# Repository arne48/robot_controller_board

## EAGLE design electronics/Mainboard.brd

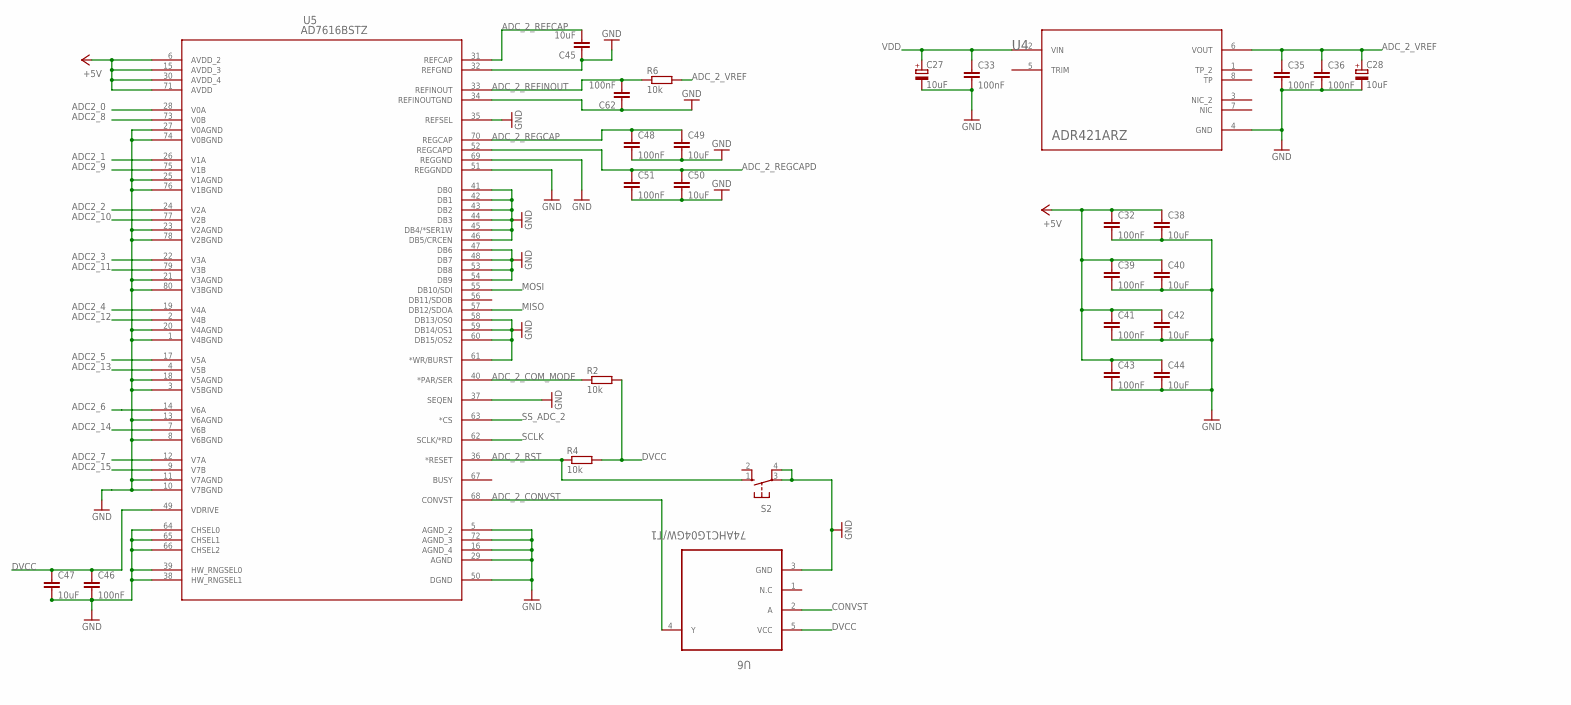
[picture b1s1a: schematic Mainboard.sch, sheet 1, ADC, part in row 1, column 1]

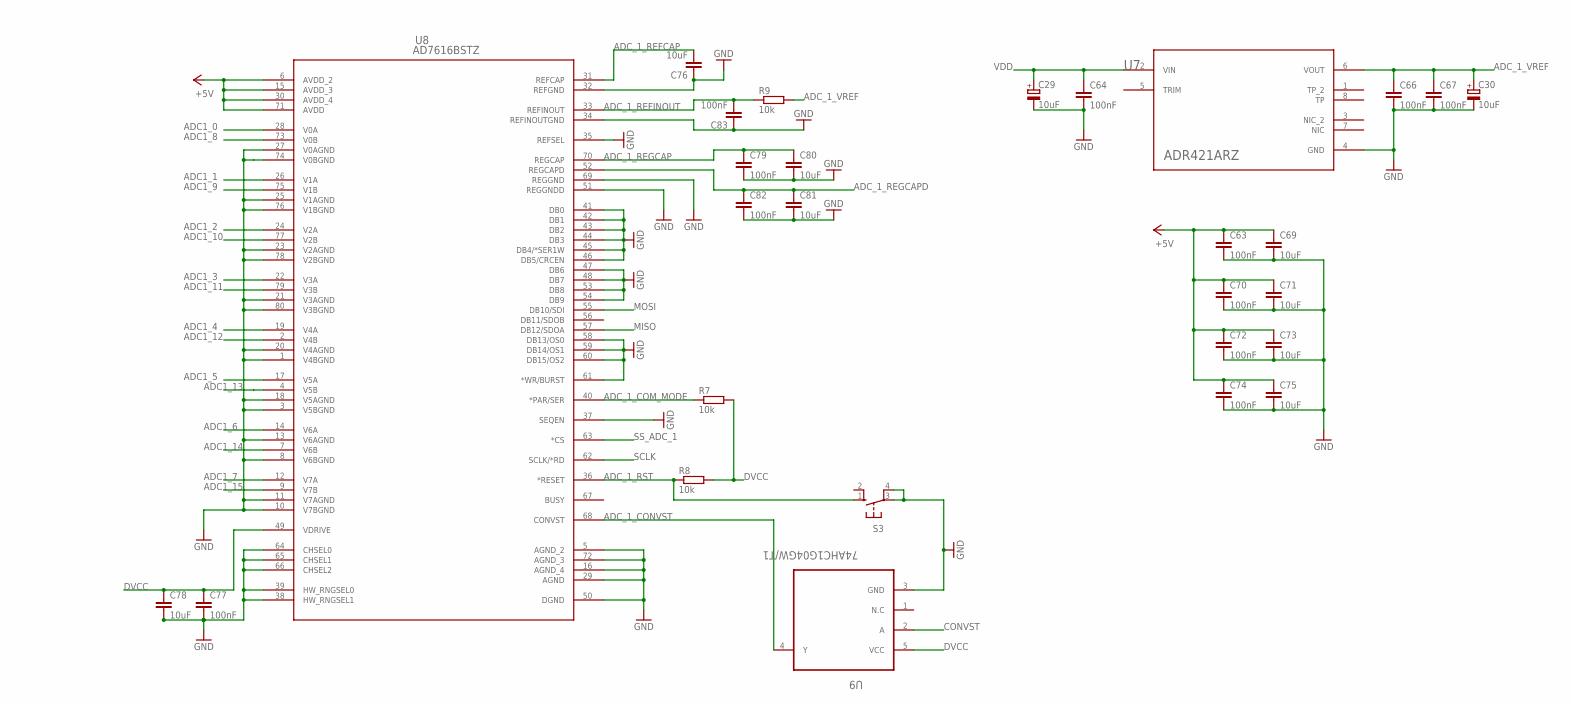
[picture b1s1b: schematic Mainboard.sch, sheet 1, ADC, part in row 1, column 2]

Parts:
C27, C28, C29, C30: 10uF; SMC_A
C32, C33, C35, C36, C39, C41, C43, C46, C48, C51, C62, C63, C64, C66, C67, C70, C72, C74, C77, C79, C82, C83: 100nF; C0603
C38, C40, C42, C44, C45, C47, C49, C50, C69, C71, C73, C75, C76, C78, C80, C81: 10uF; C0603
R2, R4, R6, R7, R8, R9: 10k; R0603
S2, S3: 10-XX; B3F-10XX
U4, U7: ADR421ARZ; R_8
U5, U8: AD7616BSTZ; ST_80_2
U6, U9: 74AHC1G04GW/T1; SOT65P210X110-5N

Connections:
+5V: C32.1, C38.1, C39.1, C40.1, C41.1, C42.1, C43.1, C44.1, C63.1, C69.1, C70.1, C71.1, C72.1, C73.1, C74.1, C75.1, U5.6 (AVDD_2), U5.15 (AVDD_3), U5.30 (AVDD_4), U5.71 (AVDD), U8.6 (AVDD_2), U8.15 (AVDD_3), U8.30 (AVDD_4), U8.71 (AVDD); also elsewhere on the board
ADC1_0: U8.28 (V0A); also elsewhere on the board
ADC1_1: U8.26 (V1A); also elsewhere on the board
ADC1_2: U8.24 (V2A); also elsewhere on the board
ADC1_3: U8.22 (V3A); also elsewhere on the board
ADC1_4: U8.19 (V4A); also elsewhere on the board
ADC1_5: U8.17 (V5A); also elsewhere on the board
ADC1_6: U8.14 (V6A); also elsewhere on the board
ADC1_7: U8.12 (V7A); also elsewhere on the board
ADC1_8: U8.73 (V0B); also elsewhere on the board
ADC1_9: U8.75 (V1B); also elsewhere on the board
ADC1_10: U8.77 (V2B); also elsewhere on the board
ADC1_11: U8.79 (V3B); also elsewhere on the board
ADC1_12: U8.2 (V4B); also elsewhere on the board
ADC1_13: U8.4 (V5B); also elsewhere on the board
ADC1_14: U8.7 (V6B); also elsewhere on the board
ADC1_15: U8.9 (V7B); also elsewhere on the board
ADC2_0: U5.28 (V0A); also elsewhere on the board
ADC2_1: U5.26 (V1A); also elsewhere on the board
ADC2_2: U5.24 (V2A); also elsewhere on the board
ADC2_3: U5.22 (V3A); also elsewhere on the board
ADC2_4: U5.19 (V4A); also elsewhere on the board
ADC2_5: U5.17 (V5A); also elsewhere on the board
ADC2_6: U5.14 (V6A); also elsewhere on the board
ADC2_7: U5.12 (V7A); also elsewhere on the board
ADC2_8: U5.73 (V0B); also elsewhere on the board
ADC2_9: U5.75 (V1B); also elsewhere on the board
ADC2_10: U5.77 (V2B); also elsewhere on the board
ADC2_11: U5.79 (V3B); also elsewhere on the board
ADC2_12: U5.2 (V4B); also elsewhere on the board
ADC2_13: U5.4 (V5B); also elsewhere on the board
ADC2_14: U5.7 (V6B); also elsewhere on the board
ADC2_15: U5.9 (V7B); also elsewhere on the board
ADC_1_COM_MODE: R7.1, U8.40 (*PAR/SER)
ADC_1_CONVST: U8.68 (CONVST), U9.4 (Y)
ADC_1_REFCAP: C76.2, U8.31 (REFCAP)
ADC_1_REFINOUT: C83.2, R9.1, U8.33 (REFINOUT)
ADC_1_REGCAP: C79.1, C80.1, U8.70 (REGCAP)
ADC_1_REGCAPD: C81.1, C82.1, U8.52 (REGCAPD)
ADC_1_RST: R8.1, S3.1 (S), U8.36 (*RESET)
ADC_1_VREF: C30.+, C66.1, C67.1, R9.2, U7.6 (VOUT)
ADC_2_COM_MODE: R2.1, U5.40 (*PAR/SER)
ADC_2_CONVST: U5.68 (CONVST), U6.4 (Y)
ADC_2_REFCAP: C45.2, U5.31 (REFCAP)
ADC_2_REFINOUT: C62.2, R6.1, U5.33 (REFINOUT)
ADC_2_REGCAP: C48.1, C49.1, U5.70 (REGCAP)
ADC_2_REGCAPD: C50.1, C51.1, U5.52 (REGCAPD)
ADC_2_RST: R4.1, S2.1 (S), U5.36 (*RESET)
ADC_2_VREF: C28.+, C35.1, C36.1, R6.2, U4.6 (VOUT)
CONVST: U6.2 (A), U9.2 (A); also elsewhere on the board
DVCC: C46.1, C47.1, C77.1, C78.1, R2.2, R4.2, R7.2, R8.2, U5.49 (VDRIVE), U6.5 (VCC), U8.49 (VDRIVE), U9.5 (VCC); also elsewhere on the board
GND: C27.-, C28.-, C29.-, C30.-, C32.2, C33.2, C35.2, C36.2, C38.2, C39.2, C40.2, C41.2, C42.2, C43.2, C44.2, C45.1, C46.2, C47.2, C48.2, C49.2, C50.2, C51.2, C62.1, C63.2, C64.2, C66.2, C67.2, C69.2, C70.2, C71.2, C72.2, C73.2, C74.2, C75.2, C76.1, C77.2, C78.2, C79.2, C80.2, C81.2, C82.2, C83.1, S2.3, S2.4 (P1), S3.3, S3.4 (P1), U4.4 (GND), U5.1 (V4BGND), U5.3 (V5BGND), U5.5 (AGND_2), U5.8 (V6BGND), U5.10 (V7BGND), U5.11 (V7AGND), U5.13 (V6AGND), U5.16 (AGND_4), U5.18 (V5AGND), U5.20 (V4AGND), U5.21 (V3AGND), U5.23 (V2AGND), U5.25 (V1AGND), U5.27 (V0AGND), U5.29 (AGND), U5.32 (REFGND), U5.34 (REFINOUTGND), U5.35 (REFSEL), U5.37 (SEQEN), U5.38 (HW_RNGSEL1), U5.39 (HW_RNGSEL0), U5.41 (DB0), U5.42 (DB1), U5.43 (DB2), U5.44 (DB3), U5.45 (DB4/*SER1W), U5.46 (DB5/CRCEN), U5.47 (DB6), U5.48 (DB7), U5.50 (DGND), U5.51 (REGGNDD), U5.53 (DB8), U5.54 (DB9), U5.58 (DB13/OS0), U5.59 (DB14/OS1), U5.60 (DB15/OS2), U5.61 (*WR/BURST), U5.64 (CHSEL0), U5.65 (CHSEL1), U5.66 (CHSEL2), U5.69 (REGGND), U5.72 (AGND_3), U5.74 (V0BGND), U5.76 (V1BGND), U5.78 (V2BGND), U5.80 (V3BGND), U6.3 (GND), U7.4 (GND), U8.1 (V4BGND), U8.3 (V5BGND), U8.5 (AGND_2), U8.8 (V6BGND), U8.10 (V7BGND), U8.11 (V7AGND), U8.13 (V6AGND), U8.16 (AGND_4), U8.18 (V5AGND), U8.20 (V4AGND), U8.21 (V3AGND), U8.23 (V2AGND), U8.25 (V1AGND), U8.27 (V0AGND), U8.29 (AGND), U8.32 (REFGND), U8.34 (REFINOUTGND), U8.35 (REFSEL), U8.37 (SEQEN), U8.38 (HW_RNGSEL1), U8.39 (HW_RNGSEL0), U8.41 (DB0), U8.42 (DB1), U8.43 (DB2), U8.44 (DB3), U8.45 (DB4/*SER1W), U8.46 (DB5/CRCEN), U8.47 (DB6), U8.48 (DB7), U8.50 (DGND), U8.51 (REGGNDD), U8.53 (DB8), U8.54 (DB9), U8.58 (DB13/OS0), U8.59 (DB14/OS1), U8.60 (DB15/OS2), U8.61 (*WR/BURST), U8.64 (CHSEL0), U8.65 (CHSEL1), U8.66 (CHSEL2), U8.69 (REGGND), U8.72 (AGND_3), U8.74 (V0BGND), U8.76 (V1BGND), U8.78 (V2BGND), U8.80 (V3BGND), U9.3 (GND); also elsewhere on the board
MISO: U5.57 (DB12/SDOA), U8.57 (DB12/SDOA); also elsewhere on the board
MOSI: U5.55 (DB10/SDI), U8.55 (DB10/SDI); also elsewhere on the board
SCLK: U5.62 (SCLK/*RD), U8.62 (SCLK/*RD); also elsewhere on the board
SS_ADC_1: U8.63 (*CS); also elsewhere on the board
SS_ADC_2: U5.63 (*CS); also elsewhere on the board
VDD: C27.+, C29.+, C33.1, C64.1, U4.2 (VIN), U7.2 (VIN); also elsewhere on the board

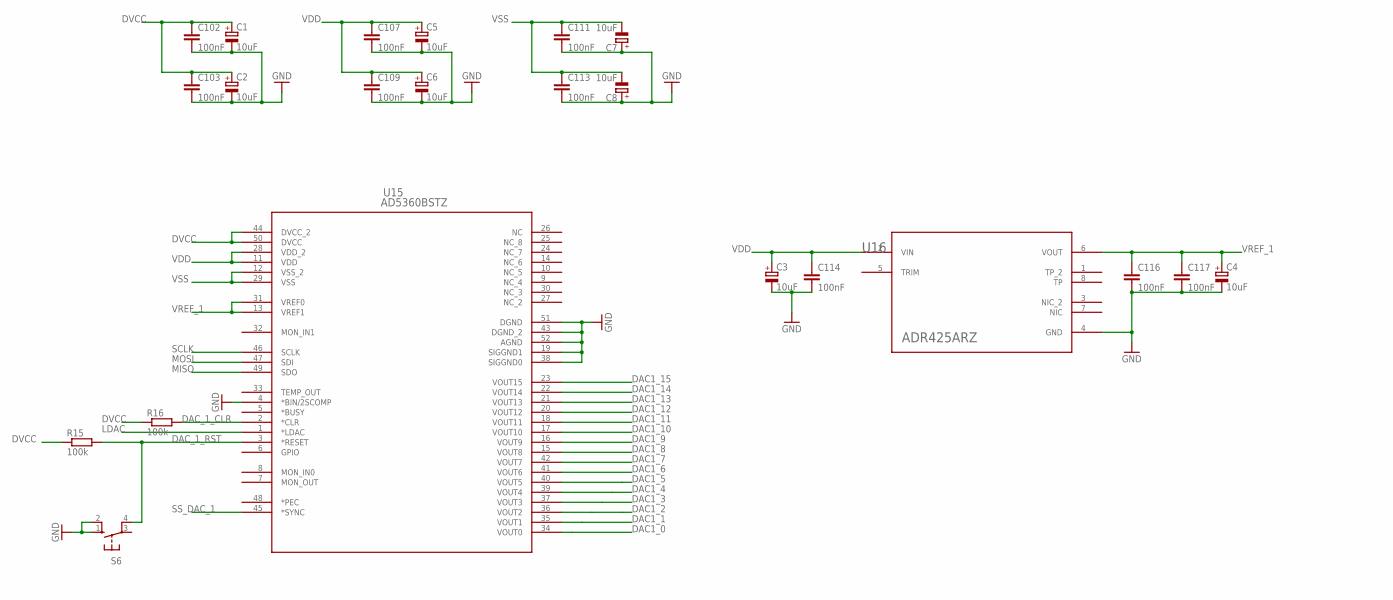
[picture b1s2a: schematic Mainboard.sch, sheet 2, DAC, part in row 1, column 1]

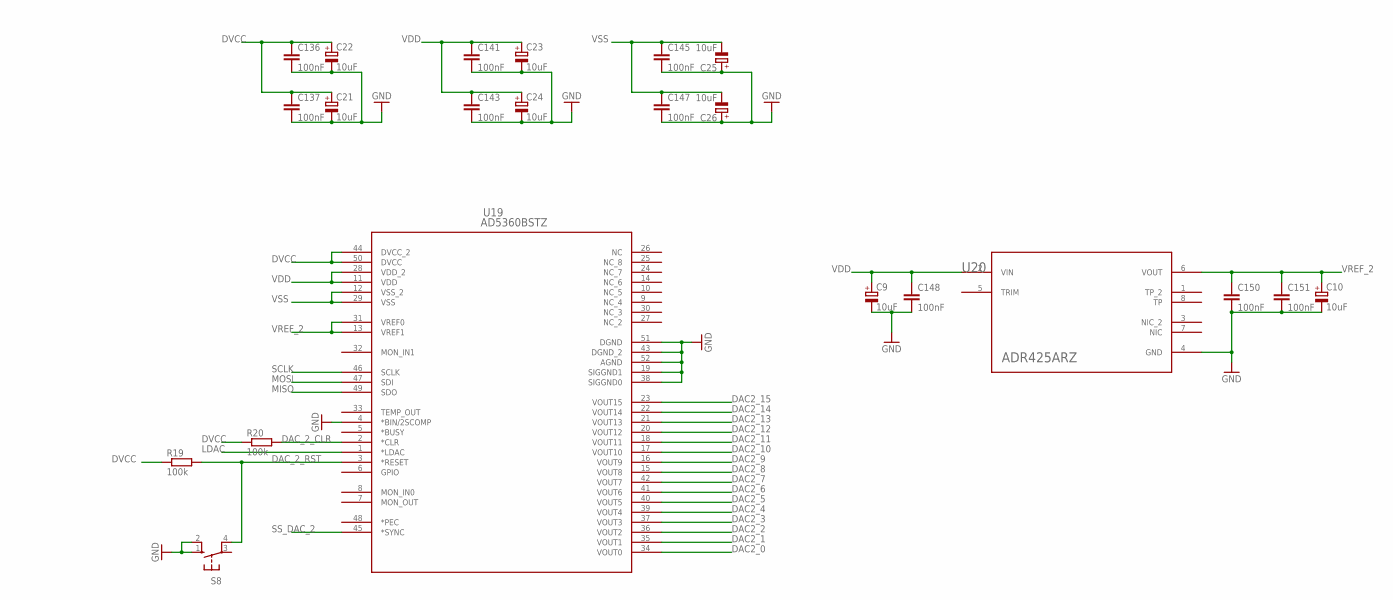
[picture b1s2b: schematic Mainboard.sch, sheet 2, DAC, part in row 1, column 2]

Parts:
C1, C2, C3, C4, C5, C6, C7, C8, C9, C10, C21, C22, C23, C24, C25, C26: 10uF; SMC_A
C102, C103, C107, C109, C111, C113, C114, C116, C117, C136, C137, C141, C143, C145, C147, C148, C150, C151: 100nF; C0603
R15, R16, R19, R20: 100k; R0603
S6, S8: 10-XX; B3F-10XX
U15, U19: AD5360BSTZ; ST_52
U16, U20: ADR425ARZ; R_8

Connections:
DAC1_0: U15.34 (VOUT0); also elsewhere on the board
DAC1_1: U15.35 (VOUT1); also elsewhere on the board
DAC1_2: U15.36 (VOUT2); also elsewhere on the board
DAC1_3: U15.37 (VOUT3); also elsewhere on the board
DAC1_4: U15.39 (VOUT4); also elsewhere on the board
DAC1_5: U15.40 (VOUT5); also elsewhere on the board
DAC1_6: U15.41 (VOUT6); also elsewhere on the board
DAC1_7: U15.42 (VOUT7); also elsewhere on the board
DAC1_8: U15.15 (VOUT8); also elsewhere on the board
DAC1_9: U15.16 (VOUT9); also elsewhere on the board
DAC1_10: U15.17 (VOUT10); also elsewhere on the board
DAC1_11: U15.18 (VOUT11); also elsewhere on the board
DAC1_12: U15.20 (VOUT12); also elsewhere on the board
DAC1_13: U15.21 (VOUT13); also elsewhere on the board
DAC1_14: U15.22 (VOUT14); also elsewhere on the board
DAC1_15: U15.23 (VOUT15); also elsewhere on the board
DAC2_0: U19.34 (VOUT0); also elsewhere on the board
DAC2_1: U19.35 (VOUT1); also elsewhere on the board
DAC2_2: U19.36 (VOUT2); also elsewhere on the board
DAC2_3: U19.37 (VOUT3); also elsewhere on the board
DAC2_4: U19.39 (VOUT4); also elsewhere on the board
DAC2_5: U19.40 (VOUT5); also elsewhere on the board
DAC2_6: U19.41 (VOUT6); also elsewhere on the board
DAC2_7: U19.42 (VOUT7); also elsewhere on the board
DAC2_8: U19.15 (VOUT8); also elsewhere on the board
DAC2_9: U19.16 (VOUT9); also elsewhere on the board
DAC2_10: U19.17 (VOUT10); also elsewhere on the board
DAC2_11: U19.18 (VOUT11); also elsewhere on the board
DAC2_12: U19.20 (VOUT12); also elsewhere on the board
DAC2_13: U19.21 (VOUT13); also elsewhere on the board
DAC2_14: U19.22 (VOUT14); also elsewhere on the board
DAC2_15: U19.23 (VOUT15); also elsewhere on the board
DAC_1_CLR: R16.2, U15.2 (*CLR)
DAC_1_RST: R15.2, S6.4 (P1), U15.3 (*RESET)
DAC_2_CLR: R20.2, U19.2 (*CLR)
DAC_2_RST: R19.2, S8.4 (P1), U19.3 (*RESET)
DVCC: C1.+, C2.+, C21.+, C22.+, C102.1, C103.1, C136.1, C137.1, R15.1, R16.1, R19.1, R20.1, U15.44 (DVCC_2), U15.50 (DVCC), U19.44 (DVCC_2), U19.50 (DVCC); also elsewhere on the board
GND: C1.-, C2.-, C3.-, C4.-, C5.-, C6.-, C7.+, C8.+, C9.-, C10.-, C21.-, C22.-, C23.-, C24.-, C25.+, C26.+, C102.2, C103.2, C107.2, C109.2, C111.2, C113.2, C114.2, C116.2, C117.2, C136.2, C137.2, C141.2, C143.2, C145.2, C147.2, C148.2, C150.2, C151.2, S6.1 (S), S6.2 (S1), S8.1 (S), S8.2 (S1), U15.4 (*BIN/2SCOMP), U15.19 (SIGGND1), U15.38 (SIGGND0), U15.43 (DGND_2), U15.51 (DGND), U15.52 (AGND), U16.4 (GND), U19.4 (*BIN/2SCOMP), U19.19 (SIGGND1), U19.38 (SIGGND0), U19.43 (DGND_2), U19.51 (DGND), U19.52 (AGND), U20.4 (GND); also elsewhere on the board
LDAC: U15.1 (*LDAC), U19.1 (*LDAC); also elsewhere on the board
MISO: U15.49 (SDO), U19.49 (SDO); also elsewhere on the board
MOSI: U15.47 (SDI), U19.47 (SDI); also elsewhere on the board
SCLK: U15.46 (SCLK), U19.46 (SCLK); also elsewhere on the board
SS_DAC_1: U15.45 (*SYNC); also elsewhere on the board
SS_DAC_2: U19.45 (*SYNC); also elsewhere on the board
VDD: C3.+, C5.+, C6.+, C9.+, C23.+, C24.+, C107.1, C109.1, C114.1, C141.1, C143.1, C148.1, U15.11 (VDD), U15.28 (VDD_2), U16.2 (VIN), U19.11 (VDD), U19.28 (VDD_2), U20.2 (VIN); also elsewhere on the board
VREF_1: C4.+, C116.1, C117.1, U15.13 (VREF1), U15.31 (VREF0), U16.6 (VOUT)
VREF_2: C10.+, C150.1, C151.1, U19.13 (VREF1), U19.31 (VREF0), U20.6 (VOUT)
VSS: C7.-, C8.-, C25.-, C26.-, C111.1, C113.1, C145.1, C147.1, U15.12 (VSS_2), U15.29 (VSS), U19.12 (VSS_2), U19.29 (VSS); also elsewhere on the board
